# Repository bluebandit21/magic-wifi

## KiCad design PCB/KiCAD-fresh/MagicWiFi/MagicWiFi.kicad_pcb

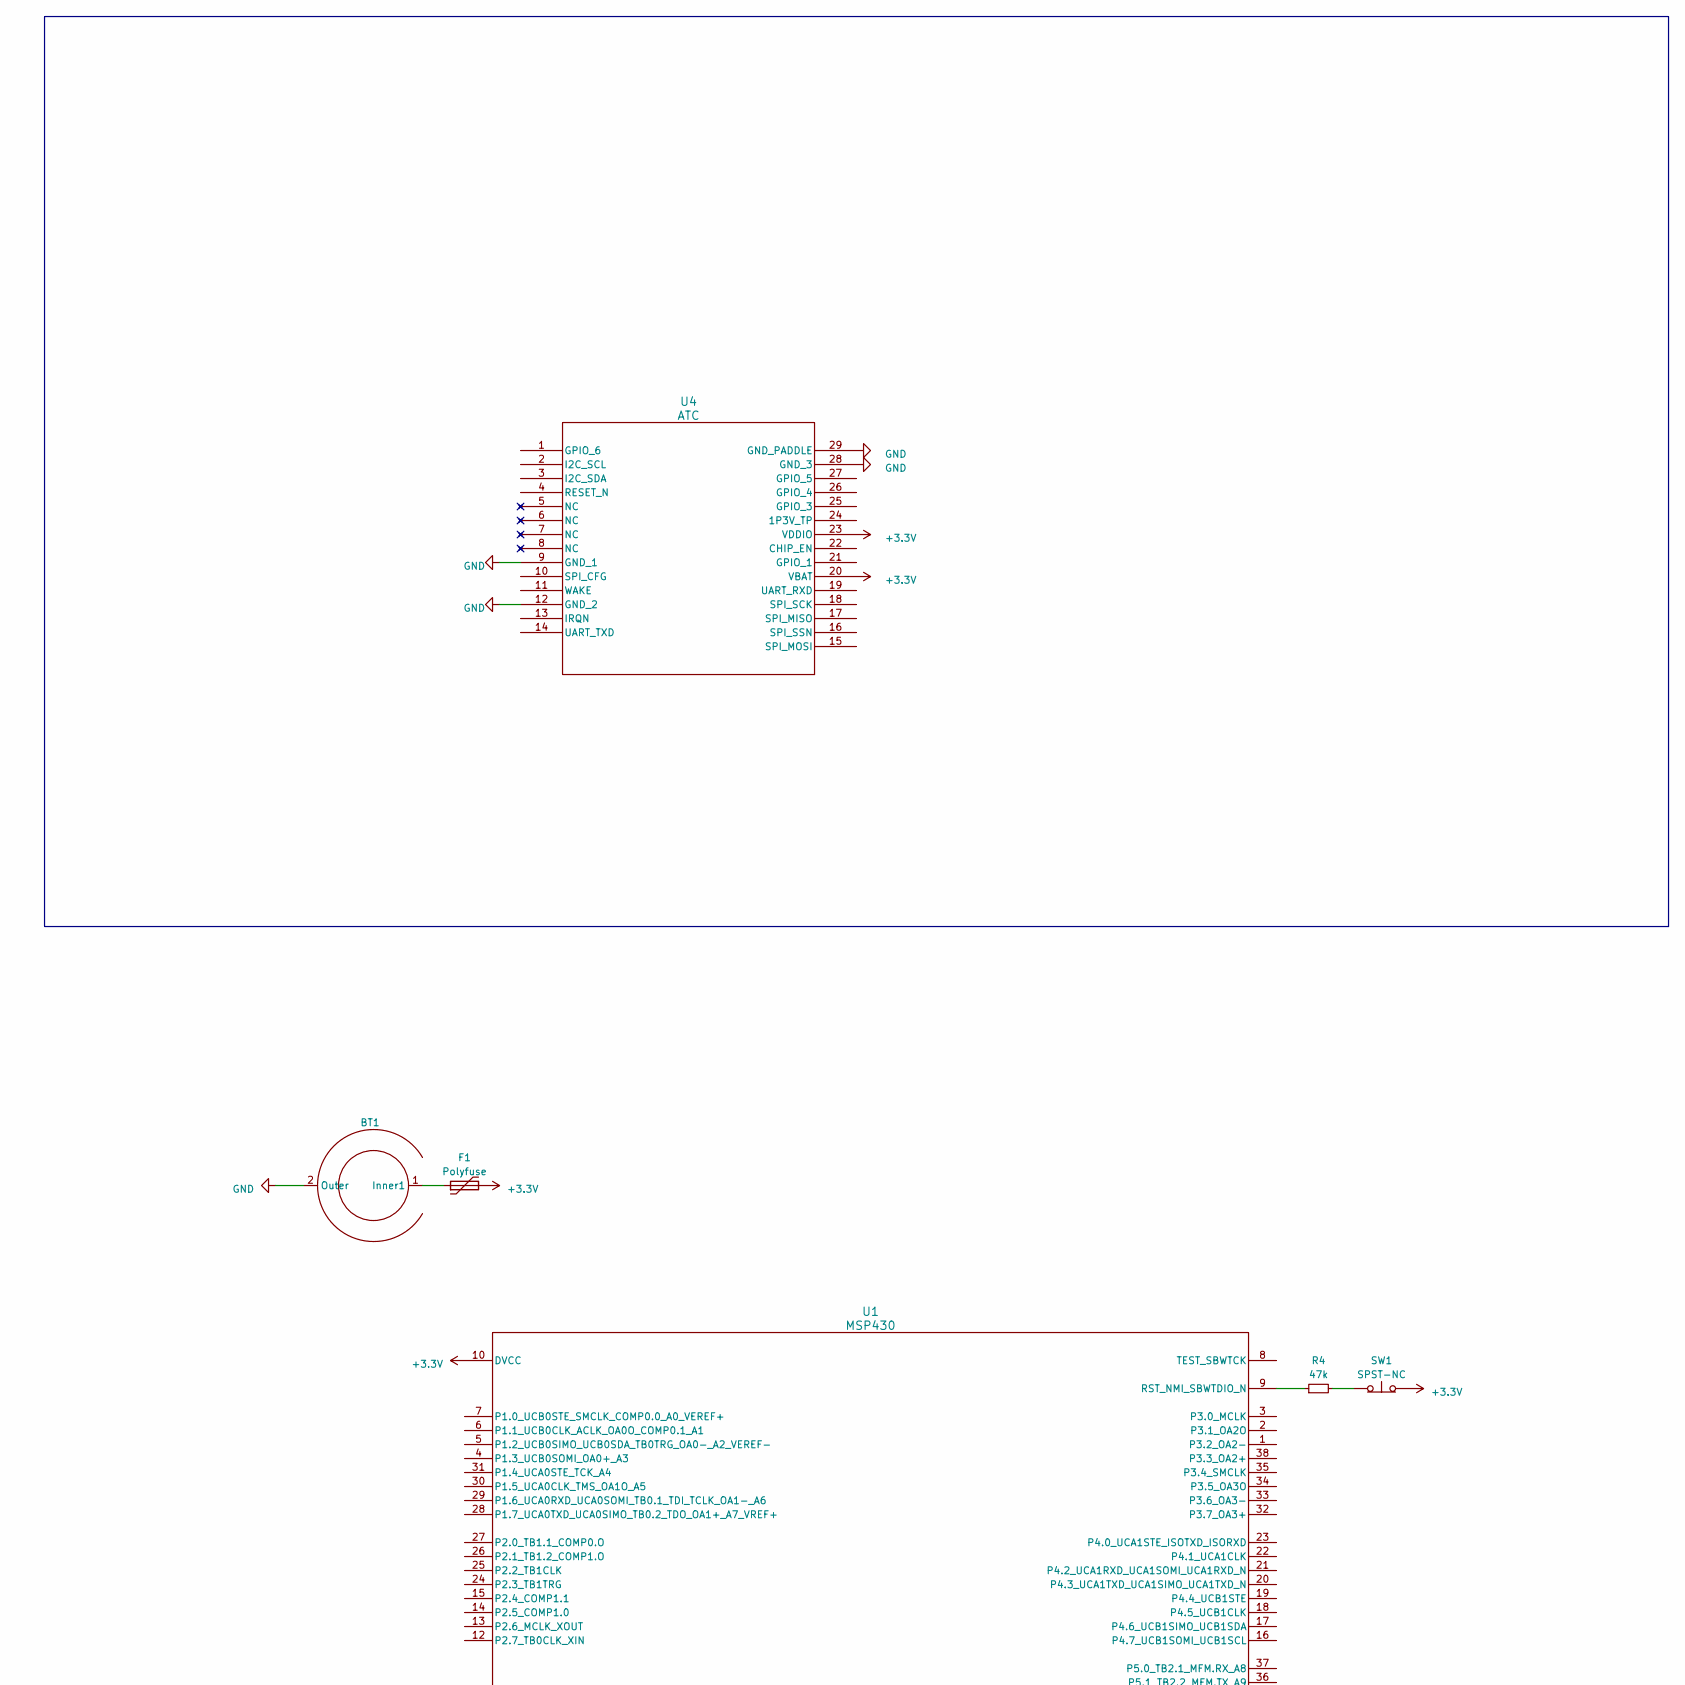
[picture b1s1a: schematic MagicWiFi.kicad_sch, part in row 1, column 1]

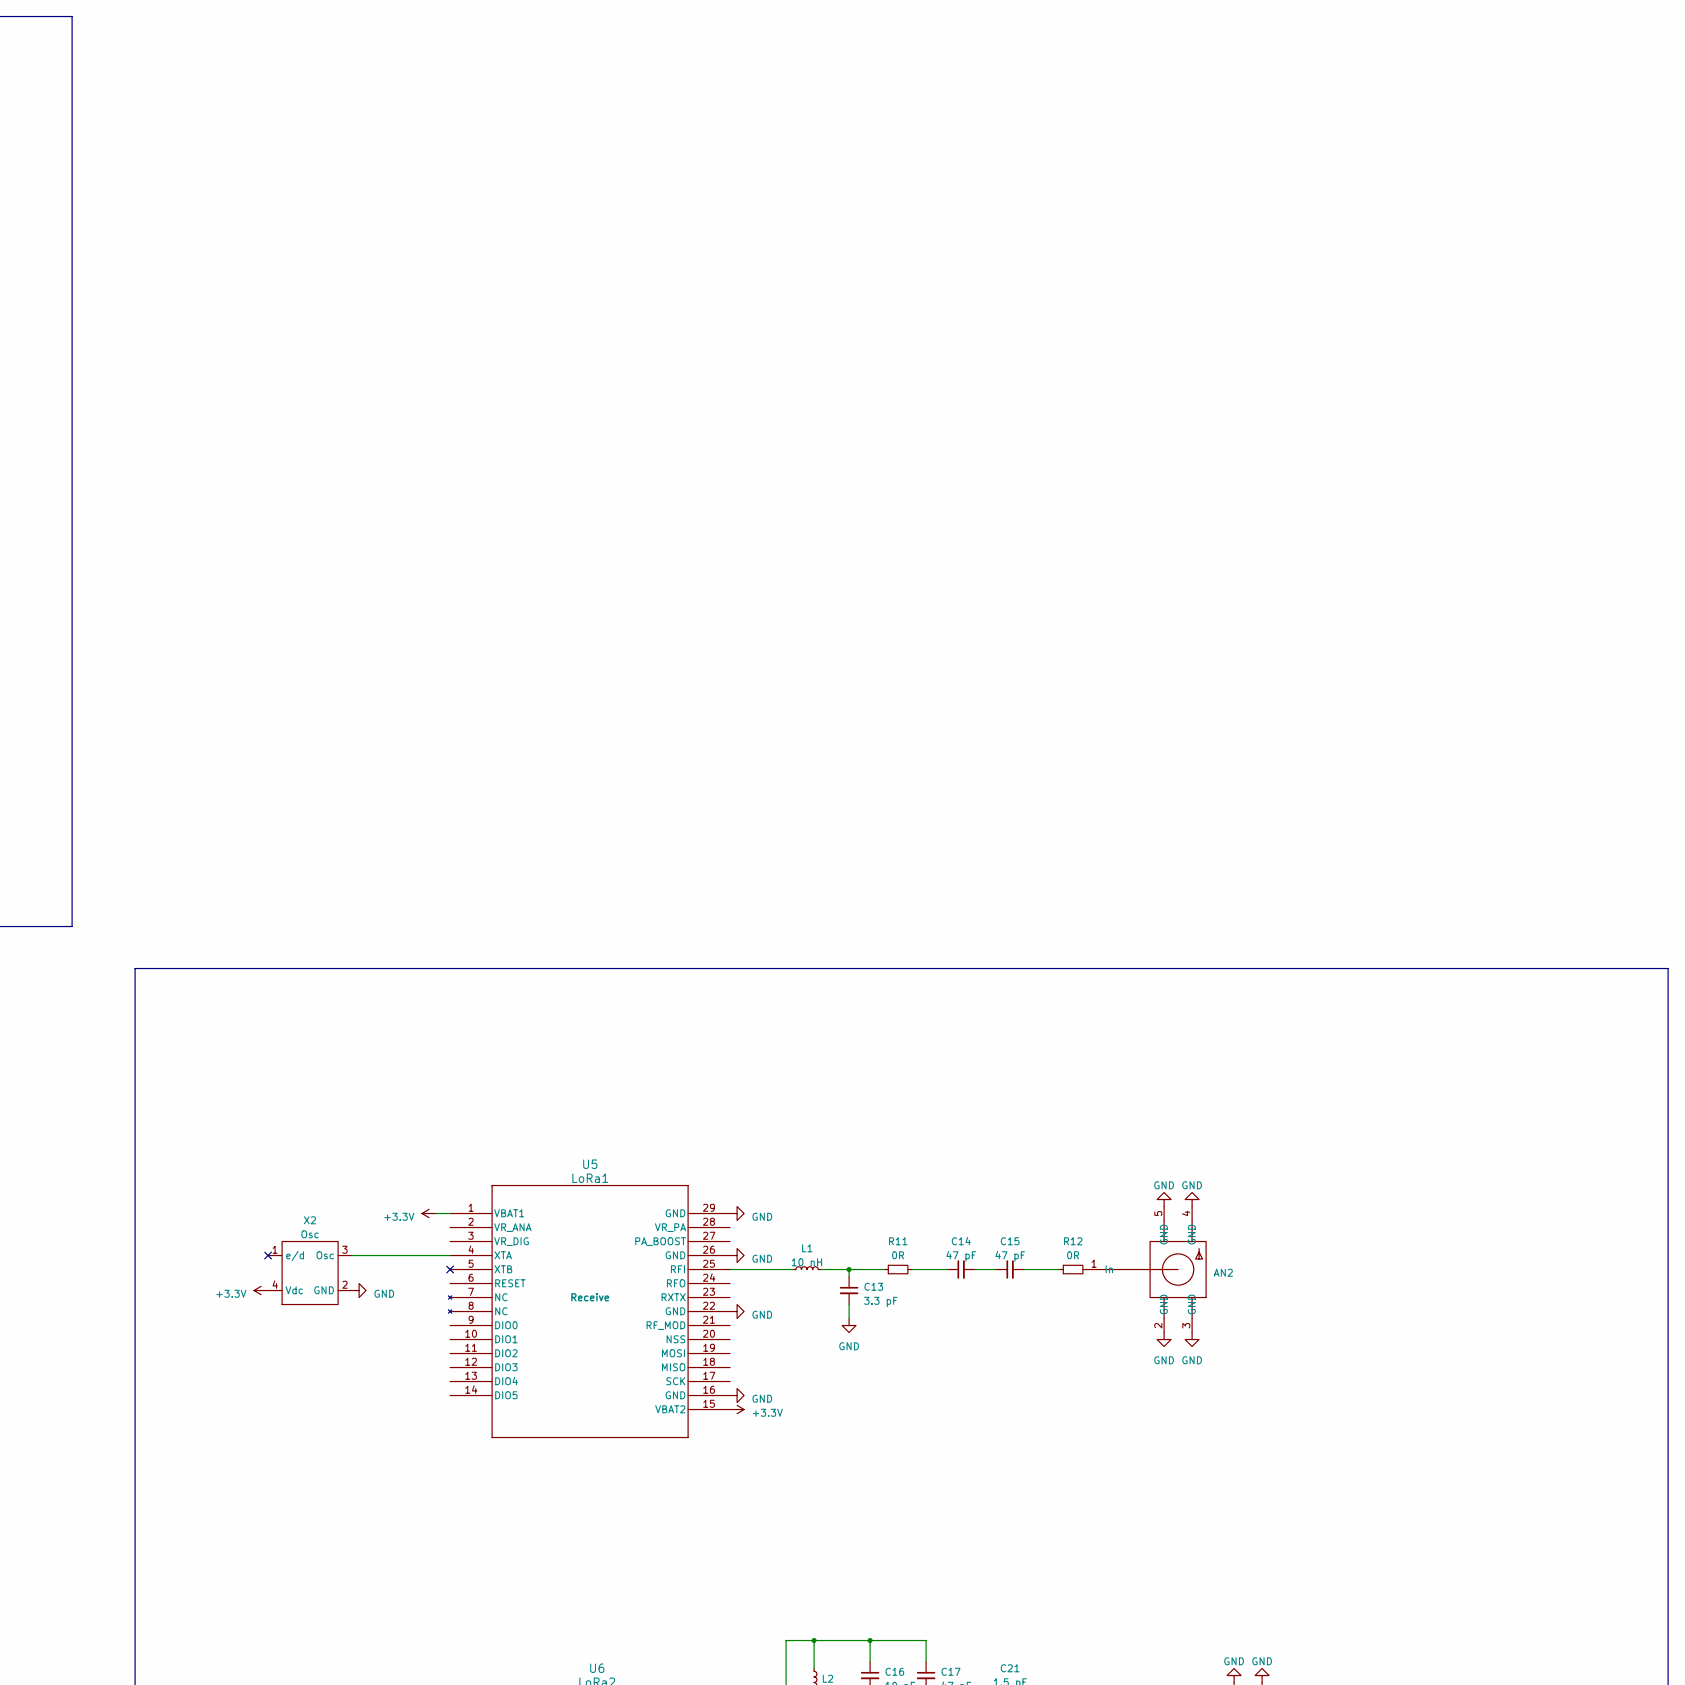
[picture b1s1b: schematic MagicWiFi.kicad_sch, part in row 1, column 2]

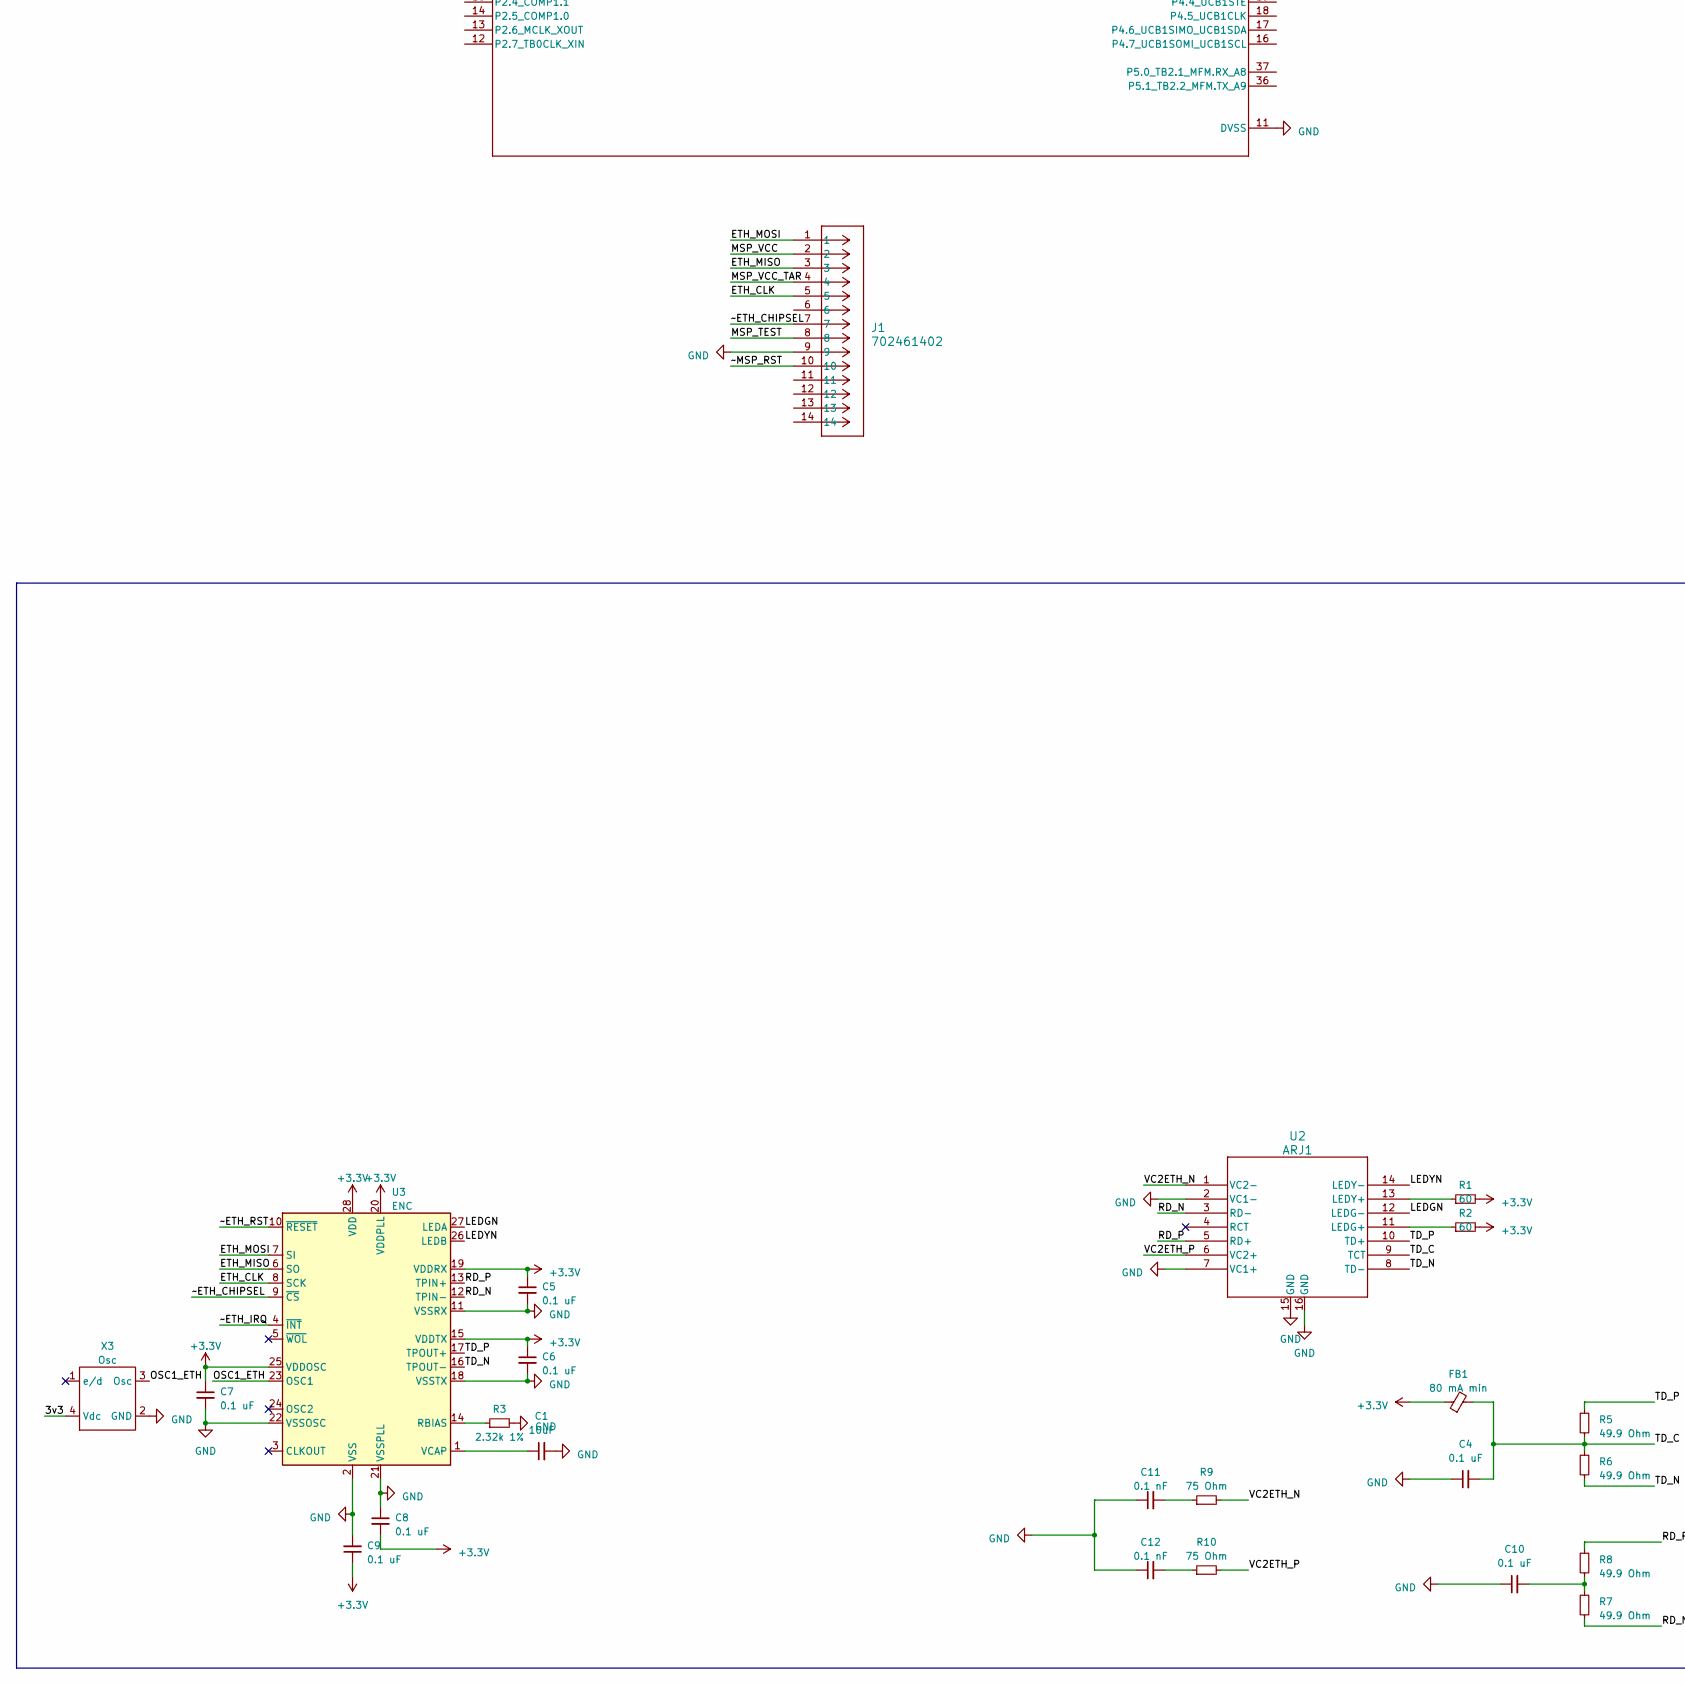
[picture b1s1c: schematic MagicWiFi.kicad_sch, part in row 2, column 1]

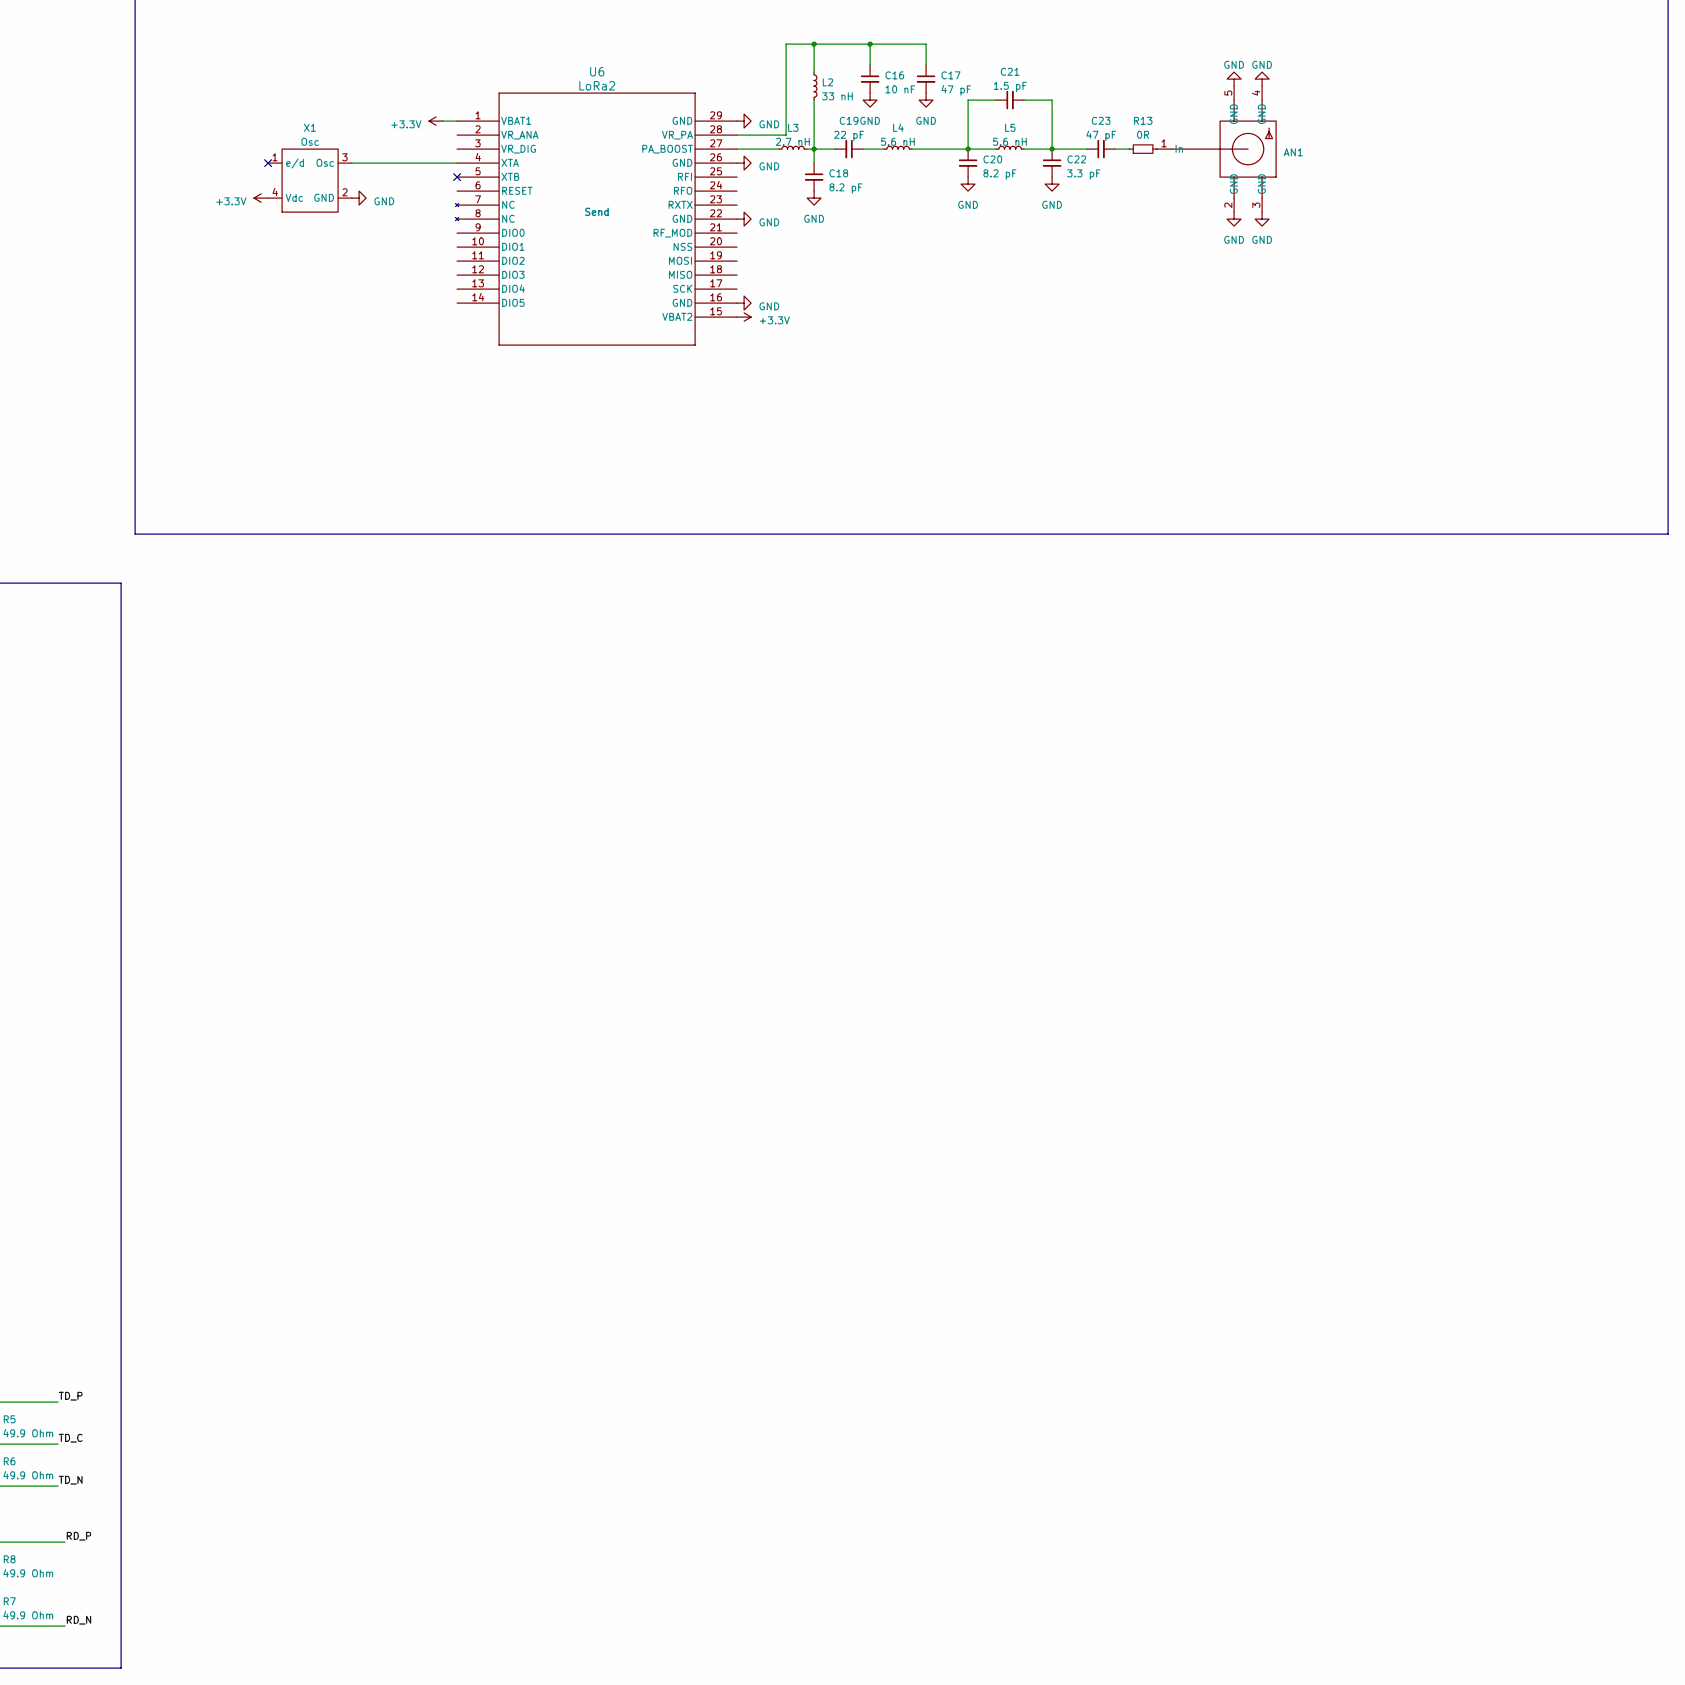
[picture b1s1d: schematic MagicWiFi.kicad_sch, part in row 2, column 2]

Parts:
AN1, AN2: SMA_EDGELAUNCH
BT1: Barrel_Conn
C1: 10uF; R_0805_2012Metric_Pad1.20x1.40mm_HandSolder
C4, C5, C6, C7, C8, C9, C10: 0.1 uF; C_0805_2012Metric
C11, C12: 0.1 nF; R_0805_2012Metric_Pad1.20x1.40mm_HandSolder
C13, C22: 3.3 pF; C_0402_1005Metric_Pad0.74x0.62mm_HandSolder; MPN GJM1555C1H3R3BB01D
C14, C15, C17, C23: 47 pF; C_0402_1005Metric_Pad0.74x0.62mm_HandSolder; MPN GJM1555C1H470JB01D
C16: 10 nF; C_0402_1005Metric_Pad0.74x0.62mm_HandSolder; MPN GRM155R71H103KA88D
C18, C20: 8.2 pF; C_0402_1005Metric_Pad0.74x0.62mm_HandSolder; MPN GJM1555C1H8R2CB01D
C19: 22 pF; C_0402_1005Metric_Pad0.74x0.62mm_HandSolder; MPN GJM1555C1H220JB01D
C21: 1.5 pF; C_0402_1005Metric_Pad0.74x0.62mm_HandSolder; MPN GJM1555C1H1R5BB01D
F1: Polyfuse; Fuse_BelFuse_0ZCJ0_1206_Metric_3216; MPN 0ZCJ0050FF2G
FB1: 80 mA min; R_0805_2012Metric_Pad1.20x1.40mm_HandSolder
J1: 702461402; CON_702461402_MOL; MPN 702461402
L1: 10 nH; C_0402_1005Metric_Pad0.74x0.62mm_HandSolder; MPN LQG15HS10NJ02D
L2: 33 nH; L_0402_1005Metric_Pad0.77x0.64mm_HandSolder; MPN LQW15AN33NJ00D
L3: 2.7 nH; L_0402_1005Metric_Pad0.77x0.64mm_HandSolder; MPN LQW15AN2N7D00D
L4, L5: 5.6 nH; L_0402_1005Metric_Pad0.77x0.64mm_HandSolder; MPN LQW15AN5N6C10D
R1, R2: 60; R_0805_2012Metric_Pad1.20x1.40mm_HandSolder
R3: 2.32k 1%; R_0805_2012Metric_Pad1.20x1.40mm_HandSolder
R4: 47k; R_0805_2012Metric_Pad1.20x1.40mm_HandSolder
R5, R6, R7, R8: 49.9 Ohm; C_0805_2012Metric
R9, R10: 75 Ohm; R_0805_2012Metric_Pad1.20x1.40mm_HandSolder
R11: 0R; R_0603_1608Metric_Pad0.98x0.95mm_HandSolder; MPN CRCW06030000Z0EA
R12, R13: 0R; R_0402_1005Metric_Pad0.72x0.64mm_HandSolder; MPN CRCW04020000Z0ED
SW1: SPST-NC; KSR223GNCLFG
U1: MSP430; DBT0038A_MSP430_N; MPN MSP430FR2355TDBTR
U2: ARJ1; ARJM11C7-114-BA-EW2_ABR; MPN ARJM11C7-114-BA-EW2
U3: ENC; SOIC-28W_7.5x17.9mm_P1.27mm; MPN ENC28J60x-SO
U4: ATC; ATWINC15x0-MR210_MCH; MPN ATWINC1500-MR210PB1952-T
U5: LoRa1; QFN28_6X6_SEM; MPN SX1272IMLTRT
U6: LoRa2; QFN28_6X6_SEM; MPN SX1272IMLTRT
X1, X2: Osc; TCXO; MPN O 32,0-JT32C-A-K-3,3-LF
X3: Osc; TCXO; MPN O 25,0-JT32C-A-K-3,3-LF

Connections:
+3.3V: C5.1, C6.1, C7.1, C8.2, C9.1, F1.2, FB1.1, R1.2, R2.2, SW1.2 (B), U1.10 (DVCC), U3.15 (VDDTX), U3.19 (VDDRX), U3.20 (VDDPLL), U3.25 (VDDOSC), U3.28 (VDD), U4.20 (VBAT), U4.23 (VDDIO), U5.1 (VBAT1), U5.15 (VBAT2), U6.1 (VBAT1), U6.15 (VBAT2), X1.4 (Vdc), X2.4 (Vdc)
/3v3: X3.4 (Vdc)
/ETH_CLK: J1.5, U3.8 (SCK)
/ETH_MISO: J1.3, U3.6 (SO)
/ETH_MOSI: J1.1, U3.7 (SI)
/LEDGN: U2.12 (LEDG-), U3.27 (LEDA)
/LEDYN: U2.14 (LEDY-), U3.26 (LEDB)
/MSP_TEST: J1.8
/MSP_VCC: J1.2
/MSP_VCC_TAR: J1.4
/OSC1_ETH: U3.23 (OSC1), X3.3 (Osc)
/RD_N: R7.2, U2.3 (RD-), U3.12 (TPIN-)
/RD_P: R8.1, U2.5 (RD+), U3.13 (TPIN+)
/TD_C: C4.2, FB1.2, R5.2, R6.1, U2.9 (TCT)
/TD_N: R6.2, U2.8 (TD-), U3.16 (TPOUT-)
/TD_P: R5.1, U2.10 (TD+), U3.17 (TPOUT+)
/VC2ETH_N: R9.2, U2.1 (VC2-)
/VC2ETH_P: R10.2, U2.6 (VC2+)
/~ETH_CHIPSEL: J1.7, U3.9 (~CS)
/~ETH_IRQ: U3.4 (~INT)
/~ETH_RST: U3.10 (~RESET)
/~MSP_RST: J1.10
GND: AN1.2 (GND), AN1.3 (GND), AN1.4 (GND), AN1.5 (GND), AN2.2 (GND), AN2.3 (GND), AN2.4 (GND), AN2.5 (GND), BT1.2 (Outer), C1.2, C4.1, C5.2, C6.2, C7.2, C8.1, C9.2, C10.1, C11.1, C12.1, C13.2, C16.2, C17.2, C18.2, C20.2, C22.2, J1.9, R3.2, U1.11 (DVSS), U2.2 (VC1-), U2.7 (VC1+), U2.15 (GND), U2.16 (GND), U3.2 (VSS), U3.11 (VSSRX), U3.18 (VSSTX), U3.21 (VSSPLL), U3.22 (VSSOSC), U4.9 (GND_1), U4.12 (GND_2), U4.28 (GND_3), U4.29 (GND_PADDLE), U5.16 (GND), U5.22 (GND), U5.26 (GND), U5.29 (GND), U6.16 (GND), U6.22 (GND), U6.26 (GND), U6.29 (GND), X1.2 (GND), X2.2 (GND), X3.2 (GND)
unnamed: AN1.1 (In), R13.2
unnamed: AN2.1 (In), R12.2
unnamed: BT1.1 (Inner1), F1.1
unnamed: C10.2, R7.1, R8.2
unnamed: C11.2, R9.1
unnamed: C12.2, R10.1
unnamed: C13.1, L1.2, R11.1
unnamed: C14.1, R11.2
unnamed: C14.2, C15.1
unnamed: C15.2, R12.1
unnamed: C18.1, C19.2, L2.2, L3.2
unnamed: C19.1, L4.1
unnamed: C20.1, C21.1, L4.2, L5.1
unnamed: C21.2, C22.1, C23.1, L5.2
unnamed: C23.2, R13.1
unnamed: R4.2, SW1.1 (A)
unnamed: R4.1, U1.9 (RST_NMI_SBWTDIO_N)
unnamed: R2.1, U2.11 (LEDG+)
unnamed: R1.1, U2.13 (LEDY+)
unnamed: R3.1, U3.14 (RBIAS)
unnamed: C1.1, U3.1 (VCAP)
unnamed: L1.1, U5.25 (RFI)
unnamed: U5.4 (XTA), X2.3 (Osc)
unnamed: L3.1, U6.27 (PA_BOOST)
unnamed: C16.1, C17.1, L2.1, U6.28 (VR_PA)
unnamed: U6.4 (XTA), X1.3 (Osc)

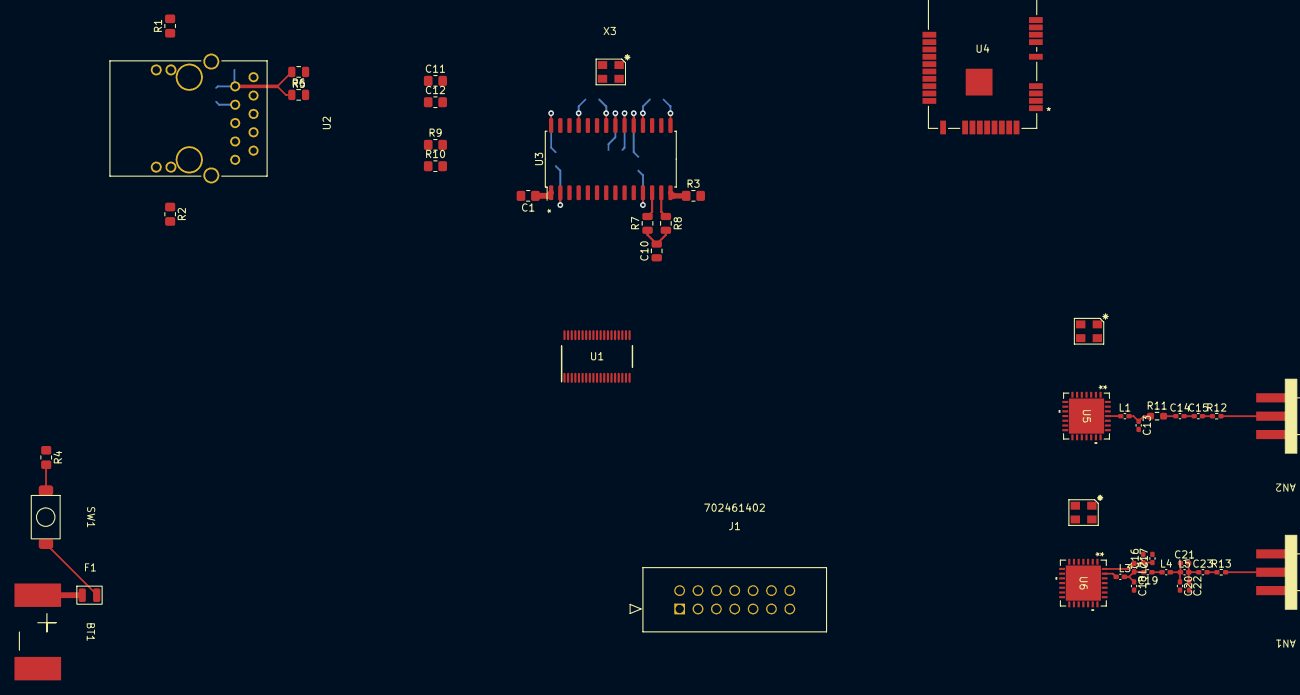
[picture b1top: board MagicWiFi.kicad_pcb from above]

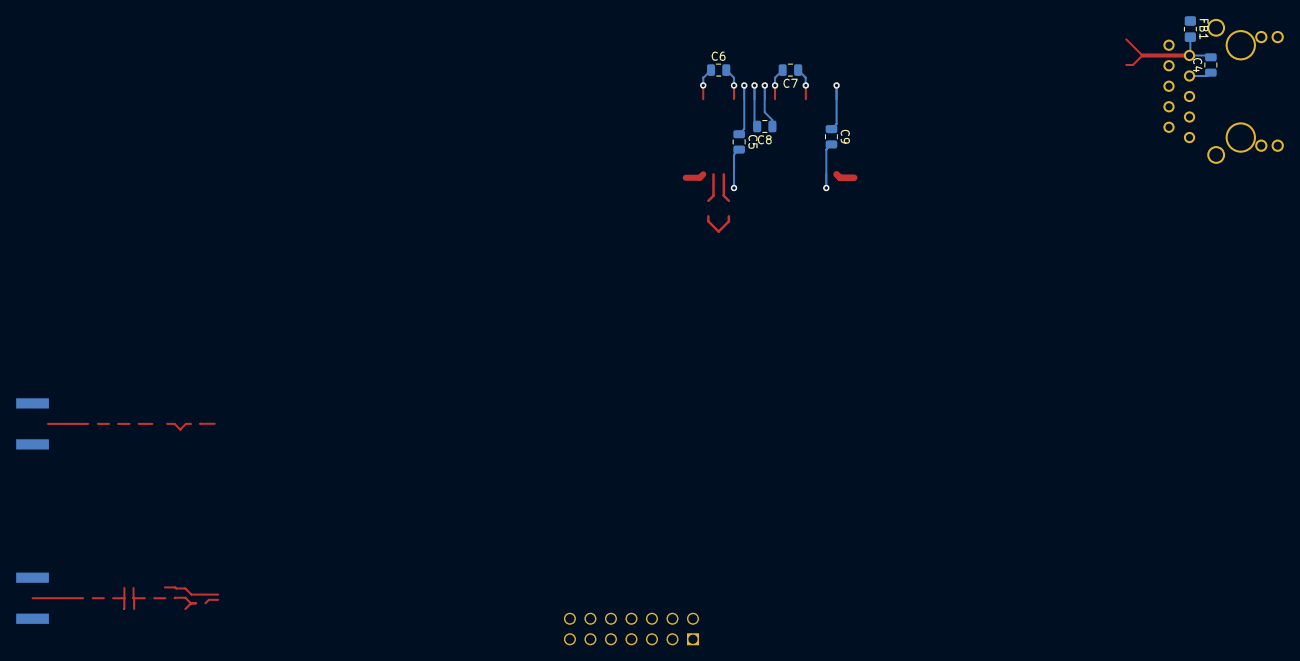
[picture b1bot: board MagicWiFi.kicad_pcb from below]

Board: 2 copper layers, 55 parts (7 on the bottom side), 42 nets.
